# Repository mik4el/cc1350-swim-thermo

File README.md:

# cc1350-swim-thermo
This project tries to create a swim thermometer broadcasting sensor data and handling interaction on dual band radio (BLE and long range sub 1 GHz) using the Texas Instrument CC1350 MCU, specifically the CC1350F128RSM. Temperature sensing is done using the high precision temperature sensor LMT70. This repo contains both software and hardware implementation.

Requires Code Composer Studio (CCS) v8 for software and Kicad for hardware. Software is programmed using the CC1350 Launchpad.

Hardware version 1.3 tested to 500m+ range with long range settings and 14dBm and simple dipole antenna to launchpad.

## How to get a cc1350 custom board "working"
1. Follow the launchpad design carefully. I sort of did that.
1. Start with soldering only the critical components for the CC1350 on the board, i.e. decoupling caps, crystals, power rail, jtag connector etc. I didn't do that but it worked anyway but I wish I did if I would have ran in to more problems.
1. Power it up with a current limited power supply and make sure there aren't any shorts. A working board should only consume a few mA.
1. Follow the steps in initial board bring up (http://processors.wiki.ti.com/index.php/CC26xx_HW_Troubleshooting) and make sure VDDR is at 1.68v, VDDS is at power supply voltage and DCOUPL is at 1.28V. It wasn't working for me initially and my VDDR was at a few mV. I got the error message (`Error connecting to the target:
(Error -242 @ 0x0)`). I found that it was due to a bad solder so adding more solder made it work. 
1. Setup the launchpad to program the board by removing all jumpers from the launchpad. Connect the 2x5-pin JTAG connector 1.27mm, I used https://www.mouser.se/ProductDetail/485-1675. Make sure the orientation is correct on the CC1350-swim-thermo (cable pointing in to the board). 
1. Open Code Composer Studio and test the connection to the board from the target config. It should just work.
1. Program the cc1350 with the hello world project that includes a modified board file in this repo and make sure the program runs as expected.
1. Success!

If you have problems, follow these debugging steps to make sure the CC1350 and board is setup as expected:

Always a good idea to cycle power and restart CCS if a previously working board stopped working.

From https://e2e.ti.com/support/wireless_connectivity/bluetooth_low_energy/f/538/p/432936/1817780): 
```
A few debugging hints (without applying power):
- Check impedance between DCDC_SW/VDDR/VDDR_RF (should be 0)
- Check impedance betwwen all 3 VDDS pins and board supply (should be 0)
- Check impedance between DCOUPL and VDDR/VDDS/GND (should be in the mega-ohm range)
- Check capacitance values from VDDR->GND (10uF) and DCOUPL->GND(1uF).
- Check current draw (when applying power). An empty device should go into boot loader mode and draw 6-7mA.
```

## Test radio on CC1350
Download and install smart rf studio http://www.ti.com/tool/SMARTRFTM-STUDIO, it includes a simple RSSI measurement and can sanity check that the radios are working as expected. It is unfortunately only available on windows. Also a good idea to have SDR or similar to validate that you are seeing radio emissions on the desired wavelengths and that they look similar to the launchpads. I recommend HackRF since it is capable of receiving both 1-6000MHz, with a normal tv-dongle SDR you will not be able to see the 2.4GHz spectrum from the CC1350.

## Software projects include:
1. `hello_CC1350_SWIMTHERMO_tirtos_ccs` - sanity check and validate that programming the board works.
1. `pinInterrupt_CC1350_SWIMTHERMO` - validate that the switch on the custom board can be read.
1. `adcsinglechannel_CC1350_SWIMTHERMO_TI` - sanity check the ADC.
1. `lmt70_CC1350_SWIMTHERMO_TI2` - validate that accurate temperature reading can be taken from the LMT70 on P1 on the board and set T_ON1 to high.
1. `tlc5973_spimaster_CC1350_SWIMTHERMO_tirtos_ccs` - turn on the onboard TLC5973 and its PSU and set a color on the LED using SPI.
1. `rfEchoRx_CC1350_SWIMTHERMO_tirtos_ccs` and `rfEchoTx_CC1350_LAUNCHXL_tirtos_ccs` tests the long range 868MHz radio between a swimthermo device and a launchpad device.
1. `full_test_CC1350_SWIMTHERMO_tirtos_ccs` combines the above projects into one (except for BLE) and more exhaustively tests all features at the same time, this .
1. `rfWsnNodeBleAdv_CC1350_LAUNCHXL_tirtos_ccs` similar to `full_test` minus TLC5973, it reads LMT70 and broadcast long range packet to `rfWsnConcentrator_CC1350_LAUNCHXL_tirtos_ccs`.
1. `rfWsnNodeBleAdv_CC1350_SWIMTHERMO_tirtos_ccs` similar to above `rfWsnNodeBleAdv_CC1350_LAUNCHXL_tirtos_ccs` but for `SWIMTHERMO`.
1. `rfWsnConcentrator_CC1350_LAUNCHXL_tirtos_ccs` concentrator for nodes built on `rfWsnNodeBleAdv_CC1350_LAUNCHXL_tirtos_ccs`.

## Todos
1. New rev of PCB with potentially input protection on gpios, external low current sleep timer using e.g. http://www.ti.com/product/TPL5111, improved contacts for termometers.

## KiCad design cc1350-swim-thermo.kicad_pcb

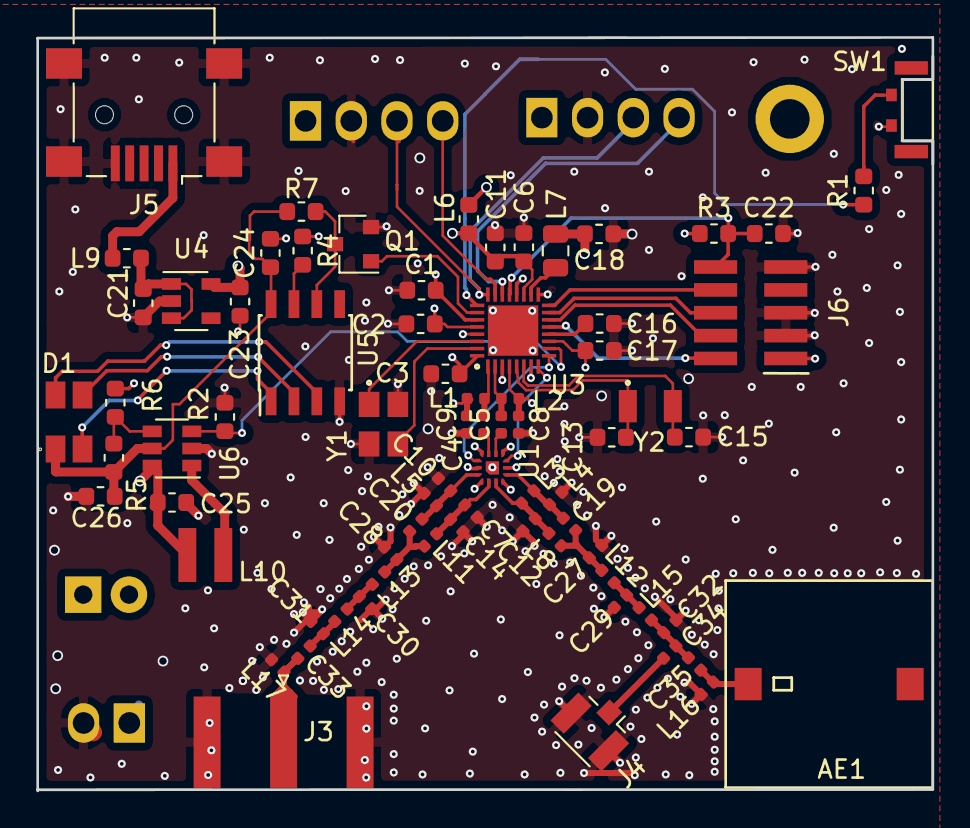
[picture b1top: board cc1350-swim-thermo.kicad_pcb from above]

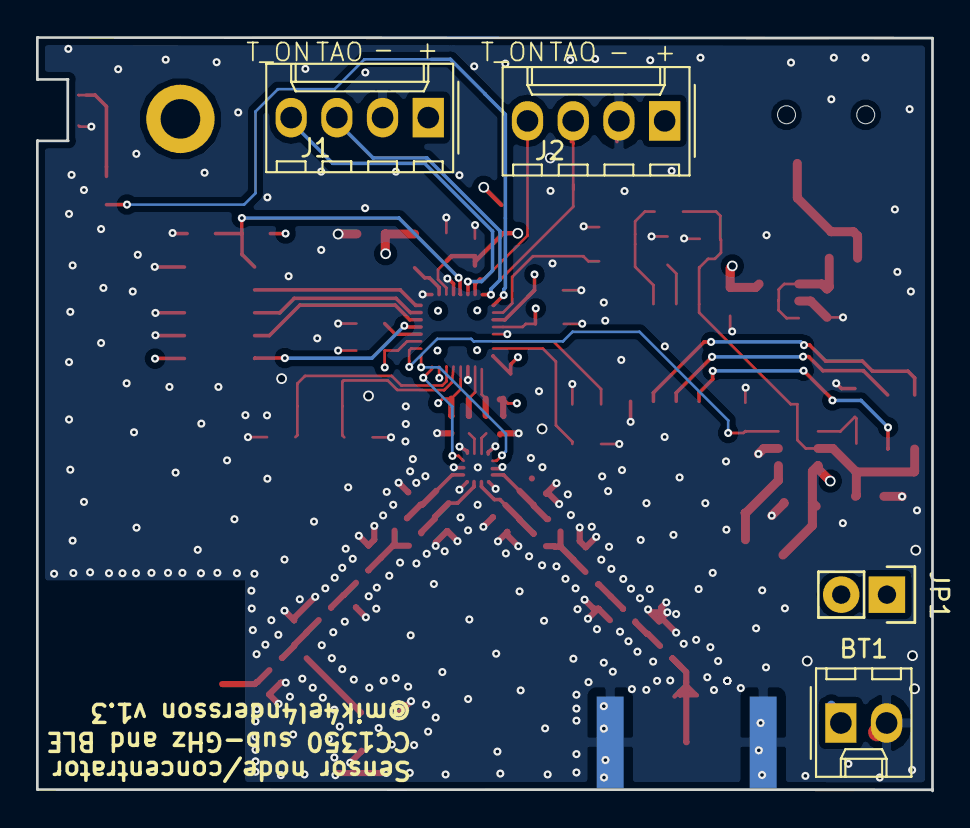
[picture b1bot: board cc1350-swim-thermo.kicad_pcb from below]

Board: 4 copper layers, 49.8 x 41.9 mm, 78 parts (4 on the bottom side), 53 nets.

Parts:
AE1: Antenna; 2450AT45A100
BT1: Battery; Molex_KK-254_AE-6410-02A_1x02_P2.54mm_Vertical
C1, C2, C3, C11, C17, C22, C23, C24: 100nF; C_0603_1608Metric
C4, C5, C8, C9: 12pF; C_0402_1005Metric
C6, C18: 22uF; C_0603_1608Metric
C7, C10, C14, C20, C28, C29: 3.6pF; C_0402_1005Metric
C12, C19, C32: 1pF; C_0402_1005Metric
C13, C15: 12pF; C_0603_1608Metric
C16, C21: 1uF; C_0603_1608Metric
C25: 4.7uF; C_0603_1608Metric
C26: 10uF; C_0603_1608Metric
C27, C34: DNM; C_0402_1005Metric
C30: 5.6pF; C_0402_1005Metric
C31: 3.3pF; C_0402_1005Metric
C33, C35: 100pF; C_0402_1005Metric
D1: ASMB-MTB0-0A3A2
J1: LMT_70_1; Molex_KK-254_AE-6410-04A_1x04_P2.54mm_Vertical
J2: LMT_70_2; Molex_KK-254_AE-6410-04A_1x04_P2.54mm_Vertical
J3: SMA; SMA_Amphenol_132289_EdgeMount
J4: U.FL; U.FL_Hirose_U.FL-R-SMT-1_Vertical
J5: USB_B_Micro; USB_Mini-B_Lumberg_2486_01_Horizontal
J6: Conn_02x05_Odd_Even; Pin_Header_Straight_SMT_02x05_1_27mm
JP1: Jumper_NC; Pin_Header_Straight_1x02
L1, L2: 10nH; L_0402_1005Metric
L3, L16, L17: DNM; L_0402_1005Metric
L4, L8, L15: 2.2nH; L_0402_1005Metric
L5, L11, L13: 6.8nH; L_0402_1005Metric
L6, L9: BLM18HE152SN1; L_0603_1608Metric
L7: 6.8uH; L_0805_2012Metric
L10: 4.7uH; VLS3015E
L12: 1.5nH; L_0402_1005Metric
L14: 7.5nH; L_0402_1005Metric
Q1: 2N7002; SOT-23
R1: 100; R_0603_1608Metric
R2, R7: 10K; R_0603_1608Metric
R3: 100K; R_0603_1608Metric
R4: 1.5K; R_0603_1608Metric
R5: 3.09M; R_0603_1608Metric
R6: 1M; R_0603_1608Metric
SW1: SW_Push; SKSLLAE010
U1: SKY13421-486LF
U3: CC1350F128RSM
U4: TLV713; SOT-23-5
U5: TLC5973; SOIC-8_3.9x4.9mm_Pitch1.27mm
U6: MCP16251; SOT-23-6
Y1: 24MHz; TSX-3225
Y2: 32.768kHz; FC-135

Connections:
+5V: C24.1, C26.1, D1.1, R5.1, R7.1, U5.8, U6.5
/2_4_RF_N: C19.2, L3.1, L4.2, U1.5
/2_4_RF_P: C12.1, L3.2, L8.2, U1.3
/868_RF_N: C7.2, C14.2, L11.1, U1.2
/868_RF_P: C10.1, C20.2, L5.1, U1.14
/BIAS_RF_N: C5.1, U1.9
/BIAS_RF_P: C4.1, U1.10
/DCDC_SW: L7.2, U3.18
/DIO0_RF_SW_PWR: U1.7, U3.8
/DIO1_RF_SW: U1.12, U3.9
/JTAG_TCKC: J6.4, U3.14
/JTAG_TDI: J6.8, U3.16
/JTAG_TDO: J6.6, U3.15
/JTAG_TMSC: J6.2, U3.13
/LED_EASYSET: Q1.1, U3.26
/PSU_ENABLE: R2.1, U3.10, U6.3
/RESET_N: C22.1, J6.10, R3.2, U3.21
/SWITCH: R1.1, U3.25
/TAO: J1.3, J2.3, U3.24
/T_ON_1: J1.4, U3.22
/T_ON_2: J2.4, U3.23
/VDDR: C2.1, C3.1, C18.1, L7.1, U3.28, U3.32
/VDDS: C1.2, C6.1, C11.2, C17.2, L6.1, U3.11, U3.19, U3.27
GND: BT1.2, C1.1, C2.2, C3.2, C6.2, C7.1, C8.2, C9.2, C10.2, C11.1, C12.2, C13.2, C14.1, C15.2, C16.1, C17.1, C18.2, C21.1, C22.2, C23.1, C24.2, C25.2, C26.2, C27.2, C28.2, C29.2, C30.2, C31.2, C32.2, J1.2, J2.2, J3.2, J4.2, J5.5, J5.6, J6.3, J6.5, J6.9, L4.1, L5.2, L16.2, L17.2, Q1.2, R2.2, R4.1, R6.2, SW1.1, U1.0, U1.1, U1.4, U1.6, U1.8, U1.11, U1.13, U3.3, U3.7, U3.17, U3.20, U3.29, U4.2, U5.4, U6.2, Y1.2, Y1.4
unnamed: AE1.1, C35.1, L16.1
unnamed: BT1.1, JP1.2
unnamed: C4.2, L1.1, U3.1
unnamed: C5.2, L2.1, U3.2
unnamed: C8.1, C9.1, L1.2, L2.2, U3.4
unnamed: C13.1, U3.5, Y2.1
unnamed: C15.1, U3.6, Y2.2
unnamed: C16.2, U3.12
unnamed: C19.1, C27.1, L8.1, L12.1
unnamed: C20.1, C28.1, L11.2, L13.1
unnamed: C21.2, L9.1, U4.1, U4.3
unnamed: C29.1, L12.2, L15.1
unnamed: C30.1, L13.2, L14.1
unnamed: C31.1, C33.2, L14.2
unnamed: C32.1, C34.2, C35.2, L15.2
unnamed: C33.1, J3.1, L17.1
unnamed: C34.1, J4.1
unnamed: D1.2, U5.3
unnamed: D1.3, U5.2
unnamed: D1.4, U5.1
unnamed: J5.1, L9.2
unnamed: L10.1, U6.1
unnamed: Q1.3, R7.2, U5.6
unnamed: R1.2, SW1.2
unnamed: R4.2, U5.7
unnamed: R5.2, R6.1, U6.4
unnamed: U3.30, Y1.1
unnamed: U3.31, Y1.3
VCC: C23.2, C25.1, J1.1, J2.1, J6.1, JP1.1, L6.2, L10.2, R3.1, U4.5, U6.6

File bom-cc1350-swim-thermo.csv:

"Source:","/Users/mikael/Code/cc1350-swim-thermo/cc1350-swim-thermo.sch"
"Date:","2018 August 30, Thursday 20:08:49"
"Tool:","Eeschema (5.0.0-3-g5ebb6b6)"
"Generator:","/private/var/folders/36/pjs3x26n38718fy5xw4bqsx00000gn/T/AppTranslocation/A9ED636F-CB78-42D0-B8FA-9596D148BDE0/d/kicad.app/Contents/SharedSupport/plugins/bom_csv_grouped_by_value_with_fp.py"
"Component Count:","78"
"Ref","Qnty","Value","Cmp name","Footprint","Description","Vendor"
"AE1, ","1","Antenna","Antenna","cc1350:2450AT45A100","Antenna symbol",""
"BT1, ","1","Battery","Battery","Connector_Molex:Molex_KK-254_AE-6410-02A_1x02_P2.54mm_Vertical","Battery (multiple cells)",""
"C1, C17, C2, C3, C24, C23, C22, ","7","100nF","C","Capacitor_SMD:C_0603_1608Metric","Unpolarized capacitor",""
"C6, C18, ","2","22uF","C","Capacitor_SMD:C_0603_1608Metric","Unpolarized capacitor",""
"C7, C10, C14, C20, C28, C29, ","6","3.6pF","C","Capacitor_SMD:C_0402_1005Metric","Unpolarized capacitor",""
"C9, C8, C4, C5, ","4","12pF","C","Capacitor_SMD:C_0402_1005Metric","Unpolarized capacitor",""
"C11, ","1","100nF","C","Capacitor_SMD:C_0402_1005Metric","Unpolarized capacitor",""
"C13, C15, ","2","12pF","C","Capacitor_SMD:C_0603_1608Metric","Unpolarized capacitor",""
"C16, C21, ","2","1uF","C","Capacitor_SMD:C_0603_1608Metric","Unpolarized capacitor",""
"C19, C12, C32, ","3","1pF","C","Capacitor_SMD:C_0402_1005Metric","Unpolarized capacitor",""
"C25, ","1","4.7uF","C","Capacitor_SMD:C_0603_1608Metric","Unpolarized capacitor",""
"C26, ","1","10uF","C","Capacitor_SMD:C_0603_1608Metric","Unpolarized capacitor",""
"C30, ","1","5.6pF","C","Capacitor_SMD:C_0402_1005Metric","Unpolarized capacitor",""
"C31, ","1","3.3pF","C","Capacitor_SMD:C_0402_1005Metric","Unpolarized capacitor",""
"C33, C35, ","2","100pF","C","Capacitor_SMD:C_0402_1005Metric","Unpolarized capacitor",""
"C34, C27, ","2","DNM","C","Capacitor_SMD:C_0402_1005Metric","Unpolarized capacitor",""
"D1, ","1","ASMB-MTB0-0A3A2","LED_ARGB","cc1350:ASMB-MTB0-0A3A2","LED RGB, common anode (pin 1)",""
"J1, ","1","LMT_70_1","Conn_01x04","Connector_Molex:Molex_KK-254_AE-6410-04A_1x04_P2.54mm_Vertical","Generic connector, single row, 01x04, script generated (kicad-library-utils/schlib/autogen/connector/)",""
"J2, ","1","LMT_70_2","Conn_01x04","Connector_Molex:Molex_KK-254_AE-6410-04A_1x04_P2.54mm_Vertical","Generic connector, single row, 01x04, script generated (kicad-library-utils/schlib/autogen/connector/)",""
"J3, ","1","SMA","Conn_Coaxial","Connector_Coaxial:SMA_Amphenol_132289_EdgeMount","coaxial connector (BNC, SMA, SMB, SMC, Cinch/RCA, ...)",""
"J4, ","1","U.FL","Conn_Coaxial","cc1350:U.FL_Hirose_U.FL-R-SMT-1_Vertical","coaxial connector (BNC, SMA, SMB, SMC, Cinch/RCA, ...)",""
"J5, ","1","USB_B_Micro","USB_B_Micro","Connector_USB:USB_Mini-B_Lumberg_2486_01_Horizontal","USB Micro Type B connector",""
"J6, ","1","Conn_02x05_Odd_Even","Conn_02x05_Odd_Even","cc1350:Pin_Header_Straight_SMT_02x05_1_27mm","Generic connector, double row, 02x05, odd/even pin numbering scheme (row 1 odd numbers, row 2 even numbers), script generated (kicad-library-utils/schlib/autogen/connector/)",""
"JP1, ","1","Jumper_NC","Jumper_NC_Small","Pin_Headers:Pin_Header_Straight_1x02","Jumper, normally closed",""
"L2, L1, ","2","10nH","L","Inductor_SMD:L_0402_1005Metric","Inductor",""
"L4, L8, L15, ","3","2.2nH","L","Inductor_SMD:L_0402_1005Metric","Inductor",""
"L5, L11, L13, ","3","6.8nH","L","Inductor_SMD:L_0402_1005Metric","Inductor",""
"L6, L9, ","2","BLM18HE152SN1","Ferrite_Bead","Inductor_SMD:L_0603_1608Metric","Ferrite bead",""
"L7, ","1","6.8uH","L","Inductor_SMD:L_0805_2012Metric","Inductor",""
"L10, ","1","4.7uH","L","cc1350:VLS3015E","Inductor",""
"L12, ","1","1.5nH","L","Inductor_SMD:L_0402_1005Metric","Inductor",""
"L14, ","1","7.5nH","L","Inductor_SMD:L_0402_1005Metric","Inductor",""
"L16, L3, L17, ","3","DNM","L","Inductor_SMD:L_0402_1005Metric","Inductor",""
"Q1, ","1","2N7002","Q_NMOS_GSD","TO_SOT_Packages_SMD:SOT-23","Transistor N-MOSFETwith substrate diode (general)",""
"R1, ","1","100","R","Resistor_SMD:R_0603_1608Metric","Resistor",""
"R2, R7, ","2","10K","R","Resistor_SMD:R_0603_1608Metric","Resistor",""
"R3, ","1","100K","R","Resistor_SMD:R_0603_1608Metric","Resistor",""
"R4, ","1","1.5K","R","Resistor_SMD:R_0603_1608Metric","Resistor",""
"R5, ","1","3.09M","R","Resistor_SMD:R_0603_1608Metric","Resistor",""
"R6, ","1","1M","R","Resistor_SMD:R_0603_1608Metric","Resistor",""
"SW1, ","1","SW_Push","SW_Push","cc1350:SKSLLAE010","Push button switch, generic, two pins",""
"U1, ","1","SKY13421-486LF","SKY13421-486LF","cc1350:SKY13421-486LF","",""
"U3, ","1","CC1350F128RSM","CC1350F128RSM","cc1350:CC1350F128RSM","",""
"U4, ","1","TLV713","TLV713","TO_SOT_Packages_SMD:SOT-23-5","",""
"U5, ","1","TLC5973","TLC5973","Housings_SOIC:SOIC-8_3.9x4.9mm_Pitch1.27mm","",""
"U6, ","1","MCP16251","MCP16251","TO_SOT_Packages_SMD:SOT-23-6","",""
"Y1, ","1","24MHz","Crystal_GND24","cc1350:TSX-3225","Four pin crystal (GND on pins 2 and 4), e.g. in SMD package",""
"Y2, ","1","32.768kHz","Crystal","cc1350:FC-135","Two pin crystal",""

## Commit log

2017-03-05 started project and made cc1350 rsm component
2017-03-07 added rf switch
2017-03-08 added schema symbols
2017-03-11 schema for rf section
2017-03-12 voltage supply rails schema
2017-03-13 external components
2017-03-15 added JTAG
2017-03-15 tidying up
2017-03-17 schema v1 ready
2017-03-18 nits
2017-03-18 started footprint association
2017-03-19 associated standard components
2017-03-19 made some footprints
2017-03-21 made all footprints
2017-03-22 started pcb layout
2017-03-23 changed balun to LFB18868MBG9E212
2017-03-25 placed all footprints and new board edge
2017-03-27 started wiring
2017-03-28 wired all mcu pads
2017-03-29 wired all components
2017-03-29 finished wiring, labels and mounting holes
2017-04-08 checked first iteration of pcb with real components
2017-04-09 zones and vias
2017-04-10 ordered pcb after small fixes
2018-04-16 Hello world template that programs to MCU
2018-04-16 Renamed to swimthermo
2018-04-17 Modified board file to create working hello world
2018-04-17 Added picture of working hello world board
2018-04-17 Cleaning up software folder
2018-04-17 Adding pinInterrupt
2018-04-17 Minimal board files
2018-04-17 Minimal button press implementation for launchpad
2018-04-17 Tested on swimthermo
2018-04-17 Initial adc project
2018-04-17 Minimal board files for ADC
2018-04-17 Meaningful printf
2018-04-17 Small fixes to get ADC to work for swimthermo
2018-04-18 Updating .gitignore
2018-04-18 Added tested project to play with lmt70 on correct port
2018-04-18 Added T_ON1 set to high
2018-04-18 updating readme
2018-04-19 Starting PSU and testing TLC5973 for first time
2018-04-19 Set pin high or low in main
2018-04-19 trying to put a meaningful bit bang delay and failing
2018-04-20 found a better bit bang delay but inconsistent timing
2018-04-22 Found a reasonable way to generate TLC5973 waveform
2018-04-23 The TLC5973 is on on all channels with spi
2018-04-23 Working TLC5973 communication
2018-04-23 Remove non functioning TLC5973 implementations
2018-04-23 Rename to swimthermo
2018-04-24 TLC5973 breath animation
2018-04-25 Testing sub ghz radio
2018-04-25 Minimal BLE adv node
2018-04-26 BLE advertising tested successfully
2018-04-26 Changed r4 value for TLC5973 current limiting experimentally
2018-05-02 long range rx/tx echo
2018-05-05 testing 625bps range
2018-05-06 PCB v1.1
2018-05-07 Create full test project and board files
2018-05-07 14dBm output enabled
2018-05-08 Animate led and cycle colors on rx
2018-05-08 Cleaning up naming of pins
2018-05-08 button press changes led animation
2018-05-09 Reading and switching between LMT70
2018-05-28 Testing dual LMT70s
2018-08-14 Soldered pcb v1.1
2018-08-14 Schema for discrete baluns and new switch
2018-08-14 Updated schema to kicad v5 and new footprints
2018-08-16 PCB v1.2 ready for manufacturing
2018-08-24 PCB sent to manufacturing
2018-08-30 updated bom
2018-09-03 pcb revision v1.3 after tests
2018-10-15 updated and tested v1.3 hardware
2019-01-20 Testing range on v1.3
2019-01-29 tested range and lmt70 on v1.3
2019-02-10 Adding node and concentrator from testing-cc1350 but ported to updated easylink
2019-02-12 showing same values on Node and Concentrator
2019-02-13 new sce program and long range radio
2019-02-15 eddystone beaconing of lmt70 data
2019-05-12 Create Swimthermo proj for node
2019-05-13 removed unnecessary pins and devices
2019-05-13 changed pins to swimthermo except for SCE
2019-05-13 Sce program for single lmt70 for swimthermo
2019-05-15 simplified code for adc
2019-05-16 SCE program for two LMT70s and better sampling
2019-05-16 Adc program with median values
2019-05-17 Two lmt70s simultaeousy
2019-05-18 verified low current
2019-05-18 save and display time since last rx in concentrator
2019-05-19 More stats on concentrator
2019-06-01 posting tlm data that gadget-eddystone-scanner can read
2019-06-02 Receiving SubGHZ then sending BLE tlm advertisements
2019-06-03 remove ble button code etc
2019-06-04 sending correct data and time since last rx in tlm
2019-06-04 sending correct data and rssi in tlm
2019-06-11 updated readme todo
2020-05-07 changing channel for temp to deployed channel
